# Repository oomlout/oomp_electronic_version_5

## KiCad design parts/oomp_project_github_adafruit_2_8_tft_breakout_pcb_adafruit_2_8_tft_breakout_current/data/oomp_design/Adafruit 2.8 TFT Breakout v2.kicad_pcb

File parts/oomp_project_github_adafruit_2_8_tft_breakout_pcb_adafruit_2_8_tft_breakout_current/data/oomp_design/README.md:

# OOMP KiCad design copy

Open `Adafruit 2.8 TFT Breakout v2.kicad_pro` (or the `.kicad_pcb` / `.kicad_sch`) in KiCad. Local OOMP libraries are under `libraries/`. Original inputs are preserved in [../original/](../original/).

Only verified unchanged installed KiCad defaults were renamed. Modified, custom, unmatched and unavailable items remain unchanged. Soldering variants are never swapped during conversion. Existing pad coordinates, nets and UUIDs are preserved.

See [conversion_report.yaml](conversion_report.yaml) for every conversion and skip. Copy this directory before editing; regeneration refuses to overwrite edited design files.

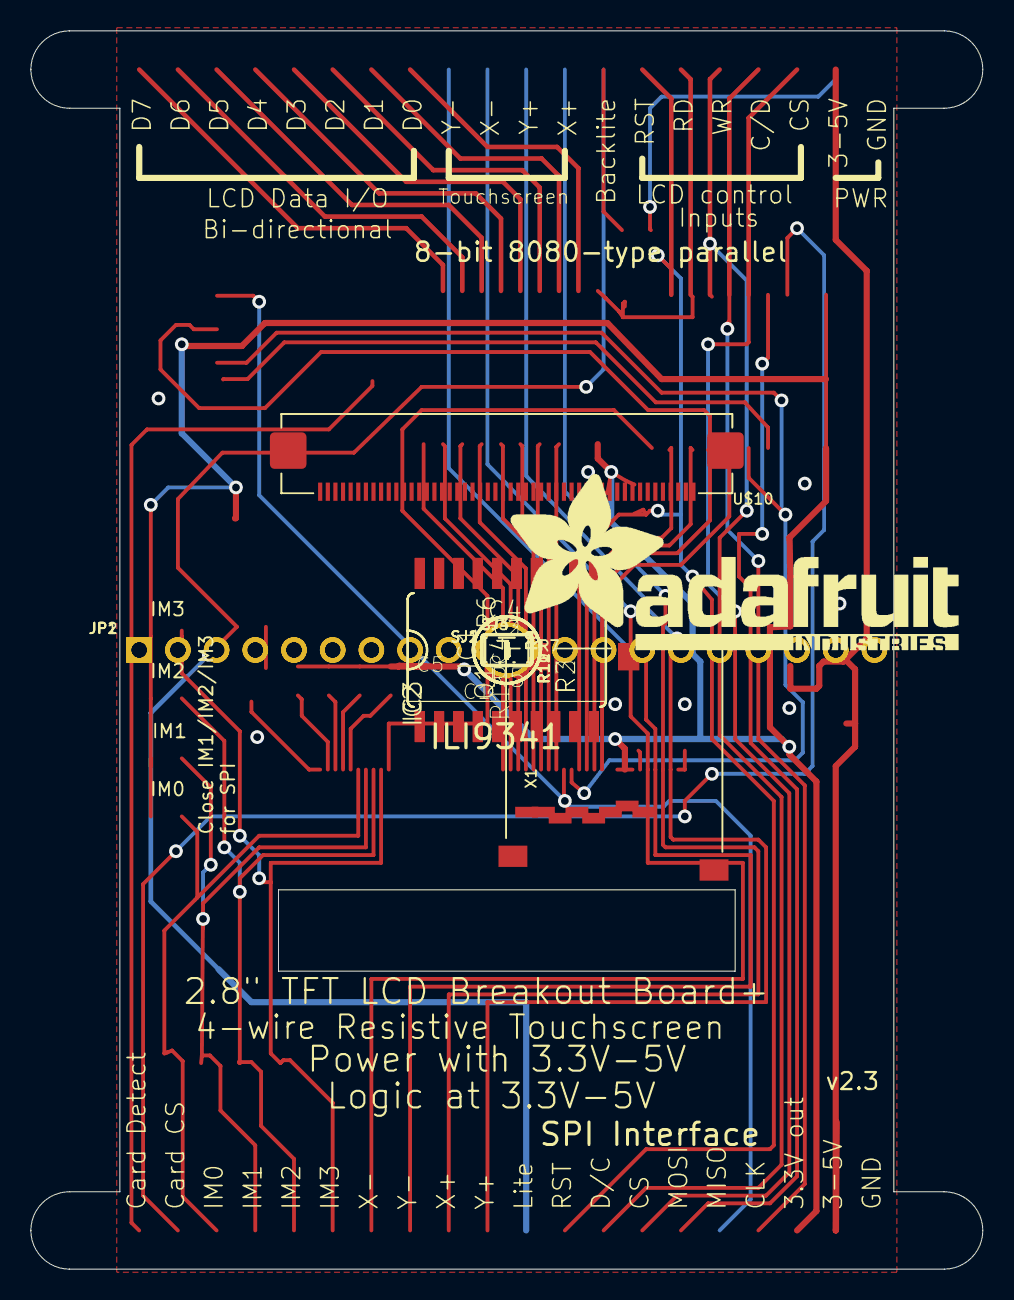
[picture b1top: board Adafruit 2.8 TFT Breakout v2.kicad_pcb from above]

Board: 16 copper layers, 62.5 x 81.3 mm, 38 parts (1 on the bottom side), 50 nets.

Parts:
C1, C4: 0.1uF; 0805-NO
C2, C3, C5: 10uF; 0805-NO
IC1: MIC5225-3.3; SOT23-5L
IC2, IC3: 74LVC245; SO20W
IC4: APX803-SAG; SOT23
JP1, JP2: 1X20_ROUND
Q1: MMBT2222; SOT23-BEC
R1, R2, R3, R4: 10; 0805-NO
R5, R7: 1K; 0805-NO
R6: 10K; R0805
R8, R9, R10, R11, R12: 10K; 0805-NO
SJ1, SJ2, SJ3, SJ4: SOLDERJUMPER_ARROW_NOPASTE
U$7, U$15, U$16, U$17: MOUNTINGHOLE3.0THIN; MOUNTINGHOLE_3.0_PLATEDTHIN
U$9, U$11, U$23: FIDUCIAL; FIDUCIAL_1MM
U$10: DISP_LCD_1.28IN_240X320_50PIN; TFT_2.83IN_240X320_50PIN
U$19: ADAFRUIT_TEXT_30MM
X1: MICROSD

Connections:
+5V: C2.1, C5.1, IC1.1, IC1.3, JP1.2, JP2.2, R7.2
CARDDET: JP2.20, X1.CD2
GND: C1.2, C2.2, C3.2, C4.2, C5.2, IC1.2, IC2.10, IC2.19, IC3.10, IC3.19, IC4.1, JP1.1, JP2.1, Q1.E, R8.1, R9.1, R10.2, R11.2, R12.1, U$10.43, U$10.48, U$10.49, U$10.50, X1.6, X1.MT1, X1.MT2
IM0: JP2.18, R8.2, SJ1.1, U$10.6
IM1: JP2.17, R9.2, SJ2.1, U$10.7
IM2: JP2.16, R11.1, SJ3.2, U$10.8
IM3: JP2.15, R10.1, SJ4.2, U$10.9
LCD_CS: IC3.15, U$10.38
LCD_CS_5V: IC3.5, JP1.3, JP2.7
LCD_DATA0: IC2.18, U$10.32
LCD_DATA0_5V: IC2.2, JP1.13
LCD_DATA1: IC2.17, U$10.31
LCD_DATA1_5V: IC2.3, JP1.14
LCD_DATA2: IC2.16, U$10.30
LCD_DATA2_5V: IC2.4, JP1.15
LCD_DATA3: IC2.15, U$10.29
LCD_DATA3_5V: IC2.5, JP1.16
LCD_DATA4: IC2.14, U$10.28
LCD_DATA4_5V: IC2.6, JP1.17
LCD_DATA5: IC2.13, U$10.27
LCD_DATA5_5V: IC2.7, JP1.18
LCD_DATA6: IC2.12, U$10.26
LCD_DATA6_5V: IC2.8, JP1.19
LCD_DATA7: IC2.11, U$10.25
LCD_DATA7_5V: IC2.9, JP1.20
LCD_LITE: JP1.8, JP2.10, R5.1, R7.1
LCD_RD: IC3.12, U$10.35
LCD_RD_5V: IC2.1, IC3.8, JP1.6, R12.2
LCD_RS: IC3.14, U$10.37, X1.5
LCD_RST: IC3.11, U$10.10
LCD_RST_5V: IC3.9, IC4.2, JP1.7, JP2.9, R6.1
LCD_RS_5V: IC3.6, JP1.4, JP2.4
LCD_WR: IC3.13, U$10.36
LCD_WR_5V: IC3.7, JP1.5, JP2.8
LCD_X+: JP1.9, JP2.12, U$10.46
LCD_X-: JP1.11, JP2.14, U$10.44
LCD_Y+: JP1.10, JP2.11, U$10.47
LCD_Y-: JP1.12, JP2.13, U$10.45
unnamed: R4.2, U$10.5
unnamed: R1.2, U$10.2
unnamed: R2.2, U$10.3
unnamed: R3.2, U$10.4
unnamed: Q1.C, U$10.1
unnamed: Q1.B, R5.2
SDI_3V: IC3.16, U$10.34, X1.3
SDI_5V: IC3.4, JP2.6
SDO: JP2.5, U$10.33, X1.7
SD_CS_3V: IC3.17, X1.2
SD_CS_5V: IC3.3, JP2.19
VCC: C1.1, C3.1, C4.1, IC1.5, IC2.20, IC3.1, IC3.20, IC4.3, JP2.3, R1.1, R2.1, R3.1, R4.1, R6.2, SJ1.2, SJ2.2, SJ3.1, SJ4.1, U$10.40, U$10.41, U$10.42, X1.4

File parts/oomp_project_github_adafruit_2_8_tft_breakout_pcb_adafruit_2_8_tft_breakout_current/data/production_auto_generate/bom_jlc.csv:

Comment,Designator,Footprint,LCSC Part #
,"JP1,JP2",Adafruit 2.8 TFT Breakout v2-import-fps:1X20_ROUND,C50981
,U$19,Adafruit 2.8 TFT Breakout v2-import-fps:ADAFRUIT_TEXT_30MM,
,X1,Adafruit 2.8 TFT Breakout v2-import-fps:MICROSD,
0.1uF,"C1,C4",Adafruit 2.8 TFT Breakout v2-import-fps:0805-NO,
10,"R1,R2,R3,R4",Adafruit 2.8 TFT Breakout v2-import-fps:0805-NO,C17415
10K,"R8,R9,R10,R11,R12",Adafruit 2.8 TFT Breakout v2-import-fps:0805-NO,C17414
10K,R6,Adafruit 2.8 TFT Breakout v2-import-fps:R0805,C17414
10uF,"C2,C3,C5",Adafruit 2.8 TFT Breakout v2-import-fps:0805-NO,
1K,"R5,R7",Adafruit 2.8 TFT Breakout v2-import-fps:0805-NO,C17513
74LVC245,"IC2,IC3",Adafruit 2.8 TFT Breakout v2-import-fps:SO20W,
APX803-SAG,IC4,Adafruit 2.8 TFT Breakout v2-import-fps:SOT23,
DISP_LCD_1.28IN_240X320_50PIN,U$10,Adafruit 2.8 TFT Breakout v2-import-fps:TFT_2.83IN_240X320_50PIN,
FIDUCIAL,"U$9,U$11,U$23",Adafruit 2.8 TFT Breakout v2-import-fps:FIDUCIAL_1MM,
MIC5225-3.3,IC1,Adafruit 2.8 TFT Breakout v2-import-fps:SOT23-5L,
MMBT2222,Q1,Adafruit 2.8 TFT Breakout v2-import-fps:SOT23-BEC,

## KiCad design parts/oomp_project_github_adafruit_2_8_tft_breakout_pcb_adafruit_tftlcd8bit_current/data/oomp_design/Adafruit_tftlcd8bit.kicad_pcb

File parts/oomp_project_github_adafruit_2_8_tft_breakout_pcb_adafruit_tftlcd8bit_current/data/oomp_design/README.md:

# OOMP KiCad design copy

Open `Adafruit_tftlcd8bit.kicad_pro` (or the `.kicad_pcb` / `.kicad_sch`) in KiCad. Local OOMP libraries are under `libraries/`. Original inputs are preserved in [../original/](../original/).

Only verified unchanged installed KiCad defaults were renamed. Modified, custom, unmatched and unavailable items remain unchanged. Soldering variants are never swapped during conversion. Existing pad coordinates, nets and UUIDs are preserved.

See [conversion_report.yaml](conversion_report.yaml) for every conversion and skip. Copy this directory before editing; regeneration refuses to overwrite edited design files.

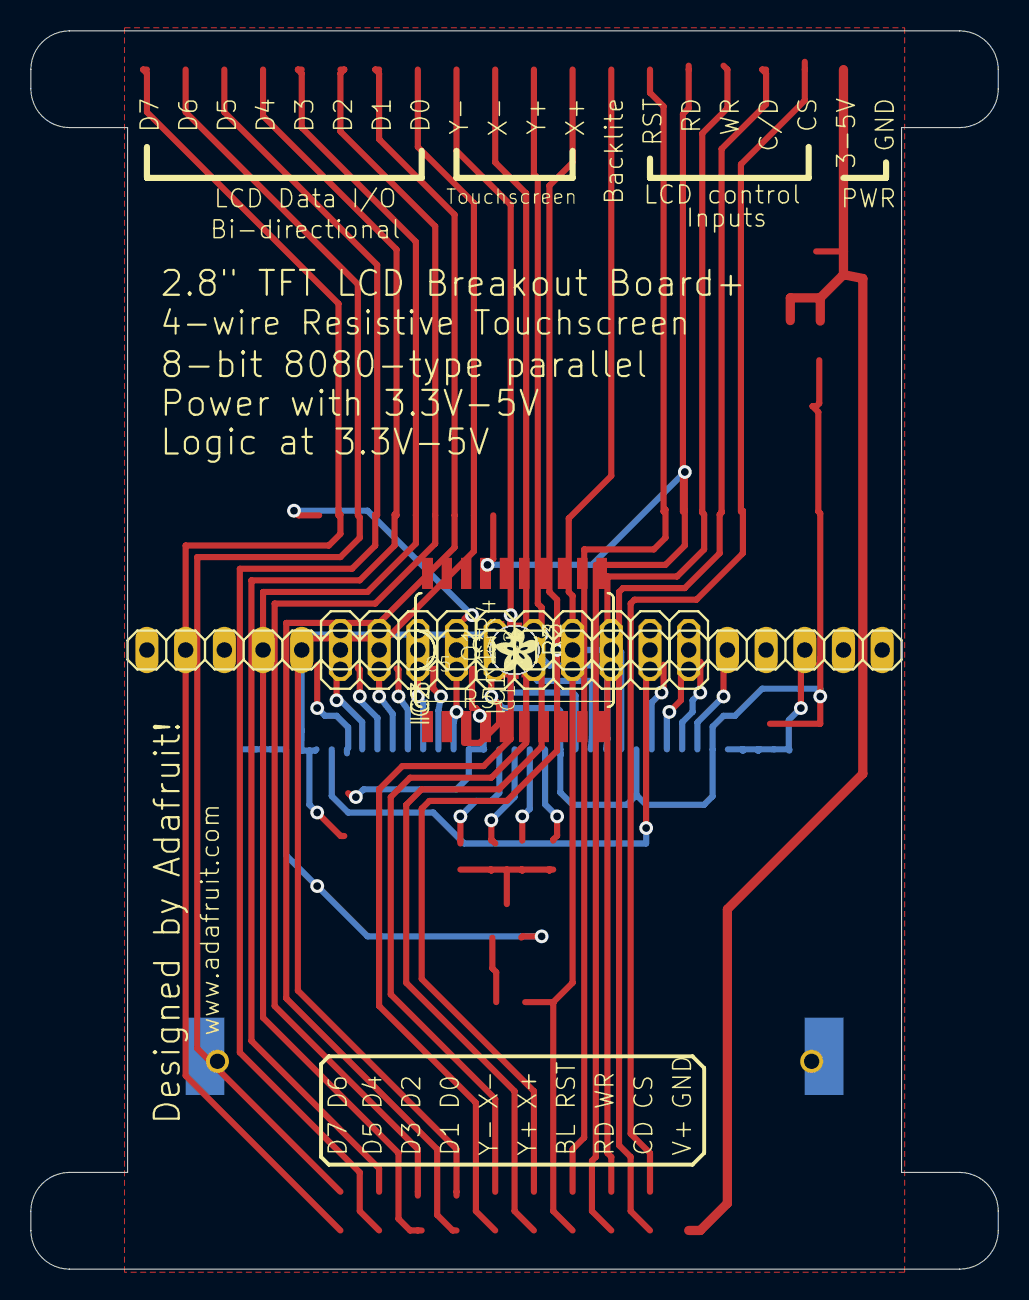
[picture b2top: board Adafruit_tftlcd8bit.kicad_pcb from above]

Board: 16 copper layers, 63.5 x 81.3 mm, 24 parts (1 on the bottom side), 40 nets.

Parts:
C1, C5: 2.2uF+; C0805K
C2, C3, C4: 0.1uF; C0805K
CN1: ILI9325_28TFT; ILI9325_28INCH_TS
IC1: LP298XS; SOT23-5L
IC2, IC3: 74ACT245DW; SO20W
Q1: 2222; SOT23-BEC
R1, R2, R3, R4: 47; R0805
R5: 1K; R0805
U$3: ADAFRUIT200MIL
U$9, U$11: FIDUCIAL; FIDUCIAL_1MM
UNK1X20BREAKOUT0: 1X20
UNK2X10BREAKOUT0: 2X10
UNK_HOLE_0: dummyfp0
UNK_HOLE_1: dummyfp1
UNK_HOLE_2: dummyfp2
UNK_HOLE_3: dummyfp3

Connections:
+5V: C5.1, IC1.1, IC1.3, UNK1X20BREAKOUT0.2, UNK2X10BREAKOUT0.2
GND: C1.2, C2.2, C3.2, C4.2, C5.2, CN1.1, CN1.2, CN1.3, CN1.4, CN1.5, CN1.21, CN1.22, CN1.34, CN1.35, CN1.36, CN1.37, IC1.2, IC2.10, IC2.19, IC3.10, IC3.19, Q1.E, UNK1X20BREAKOUT0.1, UNK2X10BREAKOUT0.1
LCD_CS: CN1.7, IC3.15
LCD_CS_5V: IC3.5, UNK1X20BREAKOUT0.3, UNK2X10BREAKOUT0.3
LCD_DATA1: CN1.23, IC2.18
LCD_DATA1_5V: IC2.2, UNK1X20BREAKOUT0.13, UNK2X10BREAKOUT0.13
LCD_DATA2: CN1.24, IC2.17
LCD_DATA2_5V: IC2.3, UNK1X20BREAKOUT0.14, UNK2X10BREAKOUT0.14
LCD_DATA3: CN1.25, IC2.16
LCD_DATA3_5V: IC2.4, UNK1X20BREAKOUT0.15, UNK2X10BREAKOUT0.15
LCD_DATA4: CN1.26, IC2.15
LCD_DATA4_5V: IC2.5, UNK1X20BREAKOUT0.16, UNK2X10BREAKOUT0.16
LCD_DATA5: CN1.27, IC2.14
LCD_DATA5_5V: IC2.6, UNK1X20BREAKOUT0.17, UNK2X10BREAKOUT0.17
LCD_DATA6: CN1.28, IC2.13
LCD_DATA6_5V: IC2.7, UNK1X20BREAKOUT0.18, UNK2X10BREAKOUT0.18
LCD_DATA7: CN1.29, IC2.12
LCD_DATA7_5V: IC2.8, UNK1X20BREAKOUT0.19, UNK2X10BREAKOUT0.19
LCD_DATA8: CN1.30, IC2.11
LCD_DATA8_5V: IC2.9, UNK1X20BREAKOUT0.20, UNK2X10BREAKOUT0.20
LCD_LITE: R5.1, UNK1X20BREAKOUT0.8, UNK2X10BREAKOUT0.8
LCD_RD: CN1.10, IC3.12
LCD_RD_5V: IC2.1, IC3.8, UNK1X20BREAKOUT0.6, UNK2X10BREAKOUT0.6
LCD_RS: CN1.8, IC3.14
LCD_RST: CN1.31, IC3.11
LCD_RST_5V: IC3.9, UNK1X20BREAKOUT0.7, UNK2X10BREAKOUT0.7
LCD_RS_5V: IC3.6, UNK1X20BREAKOUT0.4, UNK2X10BREAKOUT0.4
LCD_WR: CN1.9, IC3.13
LCD_WR_5V: IC3.7, UNK1X20BREAKOUT0.5, UNK2X10BREAKOUT0.5
LCD_X+: CN1.12, UNK1X20BREAKOUT0.9, UNK2X10BREAKOUT0.9
LCD_X-: CN1.14, UNK1X20BREAKOUT0.11, UNK2X10BREAKOUT0.11
LCD_Y+: CN1.13, UNK1X20BREAKOUT0.10, UNK2X10BREAKOUT0.10
LCD_Y-: CN1.15, UNK1X20BREAKOUT0.12, UNK2X10BREAKOUT0.12
unnamed: CN1.20, R4.2
unnamed: CN1.17, R1.2
unnamed: CN1.18, R2.2
unnamed: CN1.19, R3.2
unnamed: Q1.C, R1.1, R2.1, R3.1, R4.1
unnamed: Q1.B, R5.2
VCC: C1.1, C2.1, C3.1, C4.1, CN1.6, CN1.11, CN1.16, CN1.32, CN1.33, IC1.5, IC2.20, IC3.1, IC3.20

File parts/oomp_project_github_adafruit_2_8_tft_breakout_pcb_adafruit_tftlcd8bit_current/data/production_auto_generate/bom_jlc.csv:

Comment,Designator,Footprint,LCSC Part #
,UNK1X20BREAKOUT0,Adafruit_tftlcd8bit-import-fps:1X20,C50981
,UNK2X10BREAKOUT0,Adafruit_tftlcd8bit-import-fps:2X10,
,U$3,Adafruit_tftlcd8bit-import-fps:ADAFRUIT200MIL,
0.1uF,"C2,C3,C4",Adafruit_tftlcd8bit-import-fps:C0805K,
1K,R5,Adafruit_tftlcd8bit-import-fps:R0805,C17513
2.2uF+,"C1,C5",Adafruit_tftlcd8bit-import-fps:C0805K,
2222,Q1,Adafruit_tftlcd8bit-import-fps:SOT23-BEC,
47,"R1,R2,R3,R4",Adafruit_tftlcd8bit-import-fps:R0805,C2907268
74ACT245DW,"IC2,IC3",Adafruit_tftlcd8bit-import-fps:SO20W,
FIDUCIAL,"U$9,U$11",Adafruit_tftlcd8bit-import-fps:FIDUCIAL_1MM,
ILI9325_28TFT,CN1,Adafruit_tftlcd8bit-import-fps:ILI9325_28INCH_TS,
LP298XS,IC1,Adafruit_tftlcd8bit-import-fps:SOT23-5L,

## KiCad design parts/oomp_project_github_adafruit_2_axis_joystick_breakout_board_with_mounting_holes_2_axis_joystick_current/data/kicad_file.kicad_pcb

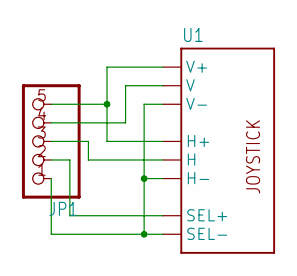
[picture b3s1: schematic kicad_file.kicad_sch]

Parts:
JP1: PINHD-1X5; 1X05
U1: JOYSTICKPTH; JOYSTICK

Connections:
unnamed: JP1.5, U1.H1 (H+), U1.V1 (V+)
unnamed: JP1.1, U1.B2A (SEL-), U1.H3 (H-), U1.V3 (V-)
unnamed: JP1.4, U1.V2 (V)
unnamed: JP1.3, U1.H2 (H)
unnamed: JP1.2, U1.B1A (SEL+)

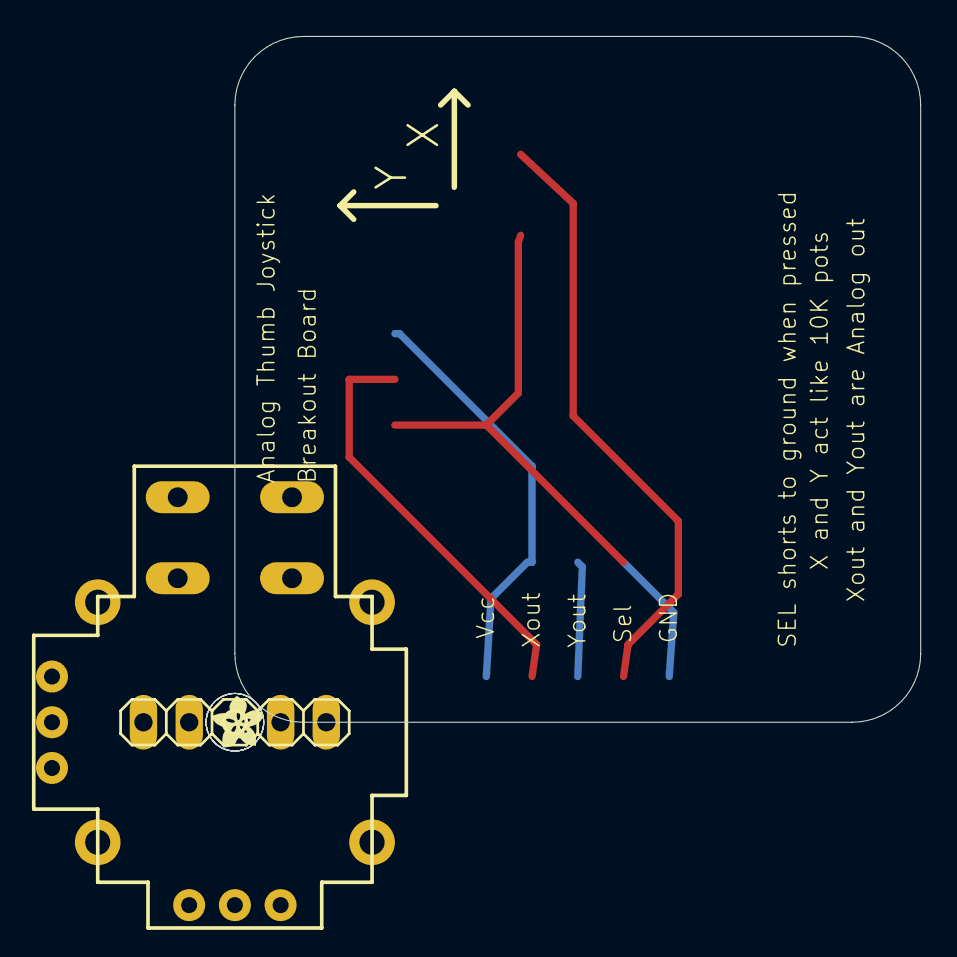
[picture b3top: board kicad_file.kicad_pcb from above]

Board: 16 copper layers, 38.1 x 38.1 mm, 7 parts (0 on the bottom side), 5 nets.

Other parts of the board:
U$1: ADAFRUIT200MIL
UNK_HOLE_0: dummyfp0
UNK_HOLE_1: dummyfp1
UNK_HOLE_2: dummyfp2
UNK_HOLE_3: dummyfp3

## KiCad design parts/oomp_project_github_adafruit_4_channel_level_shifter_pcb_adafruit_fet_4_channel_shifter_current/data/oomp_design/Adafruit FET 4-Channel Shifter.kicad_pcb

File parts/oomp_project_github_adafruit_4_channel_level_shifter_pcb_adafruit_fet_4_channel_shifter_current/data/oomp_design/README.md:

# OOMP KiCad design copy

Open `Adafruit FET 4-Channel Shifter.kicad_pro` (or the `.kicad_pcb` / `.kicad_sch`) in KiCad. Local OOMP libraries are under `libraries/`. Original inputs are preserved in [../original/](../original/).

Only verified unchanged installed KiCad defaults were renamed. Modified, custom, unmatched and unavailable items remain unchanged. Soldering variants are never swapped during conversion. Existing pad coordinates, nets and UUIDs are preserved.

See [conversion_report.yaml](conversion_report.yaml) for every conversion and skip. Copy this directory before editing; regeneration refuses to overwrite edited design files.

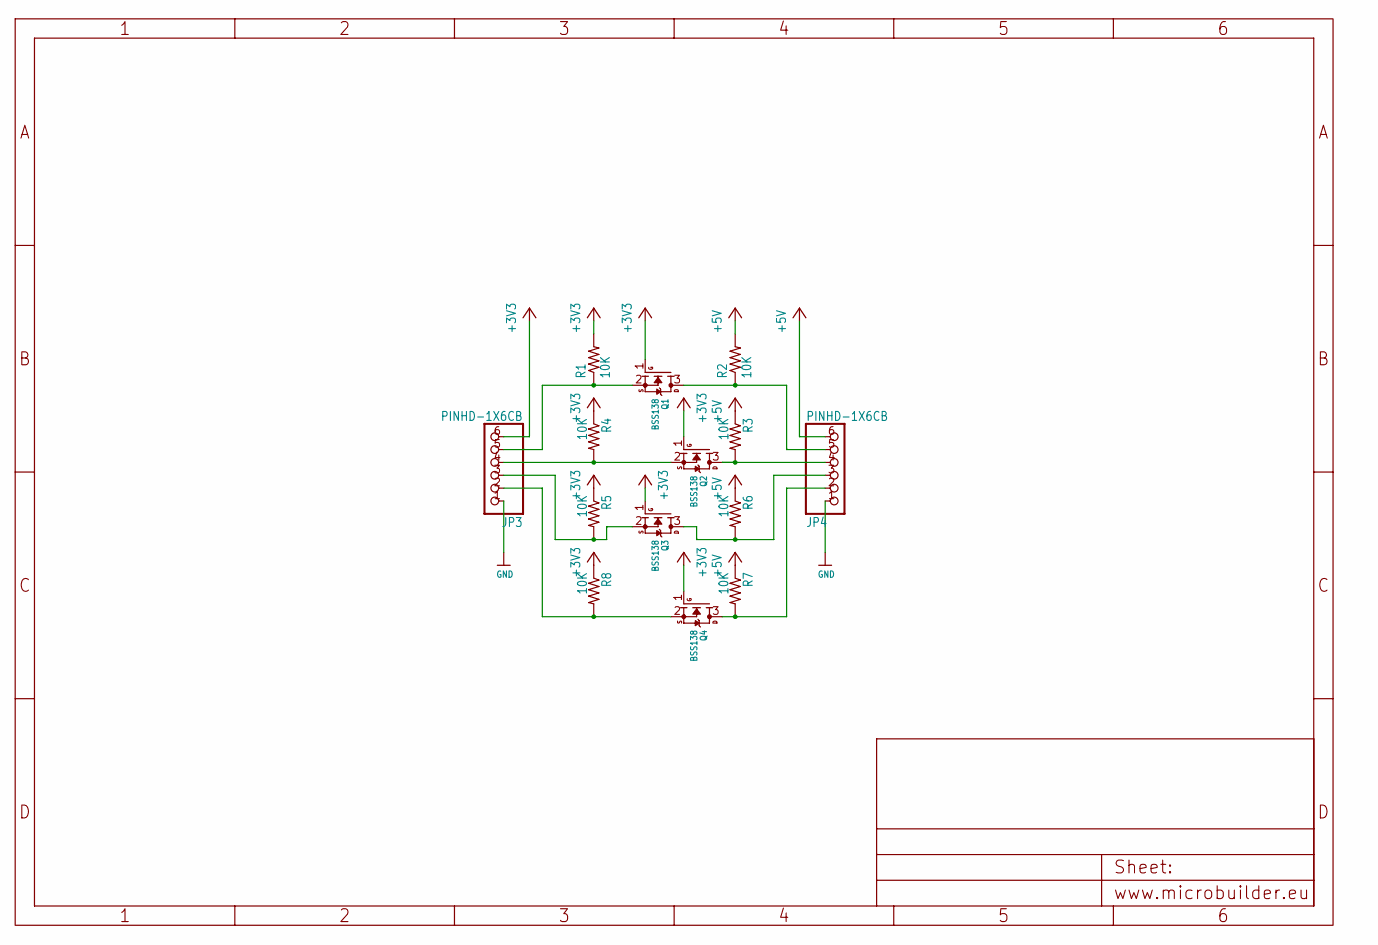
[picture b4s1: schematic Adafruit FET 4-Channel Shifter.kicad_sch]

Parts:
JP3, JP4: PINHD-1X6CB; 1X06-CLEANBIG
Q1, Q2, Q3, Q4: BSS138; SOT23
R1, R2, R3, R4, R5, R6, R7, R8: 10K; R0805

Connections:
+3V3: JP3.6, Q1.1 (G), Q2.1 (G), Q3.1 (G), Q4.1 (G), R1.2, R4.1, R5.1, R8.1
+5V: JP4.6, R2.2, R3.1, R6.1, R7.1
GND: JP3.1, JP4.1
unnamed: JP4.3, Q3.3 (D), R6.2
unnamed: JP4.5, Q1.3 (D), R2.1
unnamed: JP3.3, Q3.2 (S), R5.2
unnamed: JP3.2, Q4.2 (S), R8.2
unnamed: JP4.2, Q4.3 (D), R7.2
unnamed: JP3.4, Q2.2 (S), R4.2
unnamed: JP4.4, Q2.3 (D), R3.2
unnamed: JP3.5, Q1.2 (S), R1.1

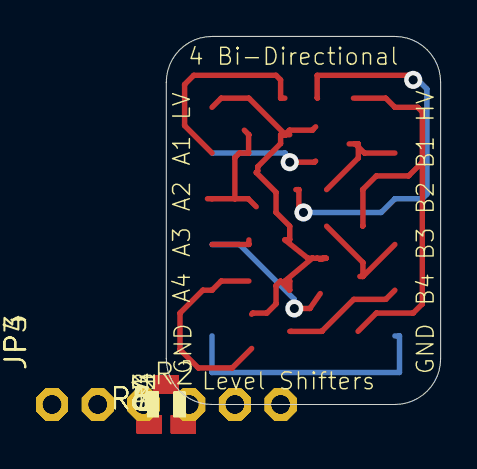
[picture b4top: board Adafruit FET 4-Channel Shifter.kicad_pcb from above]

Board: 16 copper layers, 15.2 x 20.4 mm, 15 parts (1 on the bottom side), 11 nets.

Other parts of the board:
U$1: ADAFRUIT_3.5MM

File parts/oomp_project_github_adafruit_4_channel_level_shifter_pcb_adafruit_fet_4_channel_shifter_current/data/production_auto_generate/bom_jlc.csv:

Comment,Designator,Footprint,LCSC Part #
,"JP3,JP4",Adafruit FET 4-Channel Shifter-import-fps:1X06-CLEANBIG,C37208
,U$1,Adafruit FET 4-Channel Shifter-import-fps:ADAFRUIT_3.5MM,
10K,"R1,R2,R3,R4,R5,R6,R7,R8",Adafruit FET 4-Channel Shifter-import-fps:R0805,C17414
BSS138,"Q1,Q2,Q3,Q4",Adafruit FET 4-Channel Shifter-import-fps:SOT23,C52895
